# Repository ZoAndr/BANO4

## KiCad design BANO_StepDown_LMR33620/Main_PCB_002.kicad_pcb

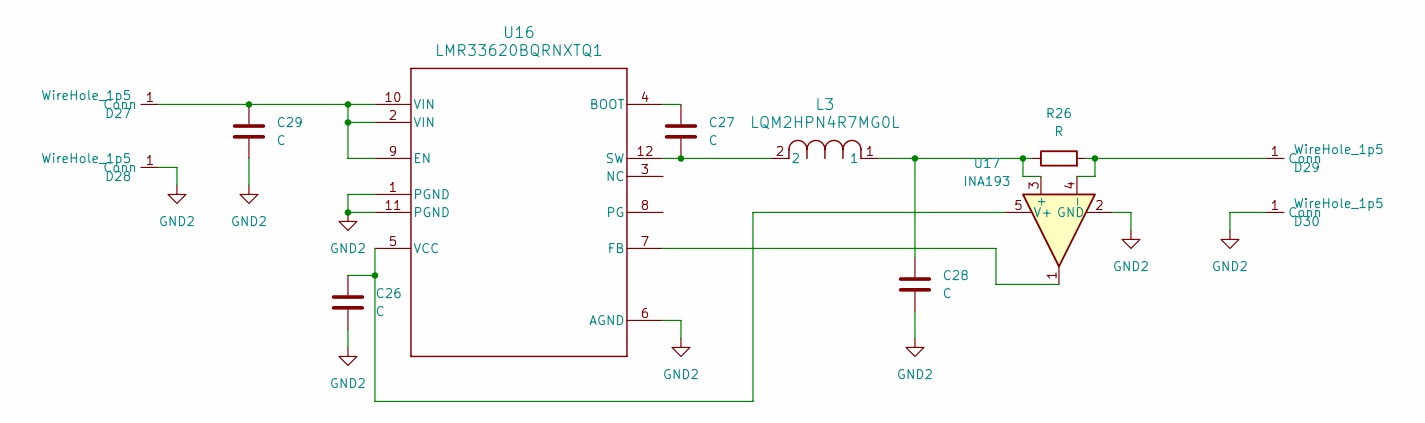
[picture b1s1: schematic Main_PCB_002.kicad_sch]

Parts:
C26, C27: C; C_0603_1608Metric_Pad1.08x0.95mm_HandSolder
C28, C29: C; C_0805_2012Metric_Pad1.18x1.45mm_HandSolder
D27, D28, D29, D30: WireHole_1p5; WireHole_1p2
L3: LQM2HPN4R7MG0L; IND_LQM2HPN4R7MG0L_MUR
R26: R; R_0603_1608Metric_Pad0.98x0.95mm_HandSolder
U16: LMR33620BQRNXTQ1; RNX0012B
U17: INA193; SOT-23-5

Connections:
GND2: C26.2, C28.2, C29.2, D28.1 (Conn), D30.1 (Conn), U16.1 (PGND), U16.6 (AGND), U16.11 (PGND), U17.2 (GND)
unnamed: C29.1, D27.1 (Conn), U16.2 (VIN), U16.9 (EN), U16.10 (VIN)
unnamed: D29.1 (Conn), R26.2, U17.4 (-)
unnamed: C27.1, U16.4 (BOOT)
unnamed: U16.7 (FB), U17.1
unnamed: C27.2, L3.2, U16.12 (SW)
unnamed: C26.1, U16.5 (VCC), U17.5 (V+)
unnamed: C28.1, L3.1, R26.1, U17.3 (+)

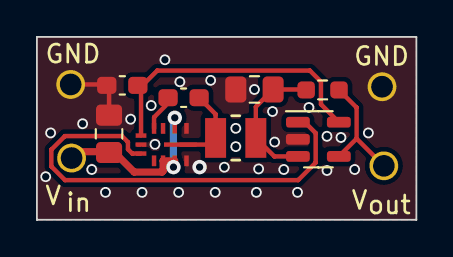
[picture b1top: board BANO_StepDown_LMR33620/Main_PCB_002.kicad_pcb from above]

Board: 2 copper layers, 21.1 x 10.2 mm, 12 parts (0 on the bottom side), 8 nets.

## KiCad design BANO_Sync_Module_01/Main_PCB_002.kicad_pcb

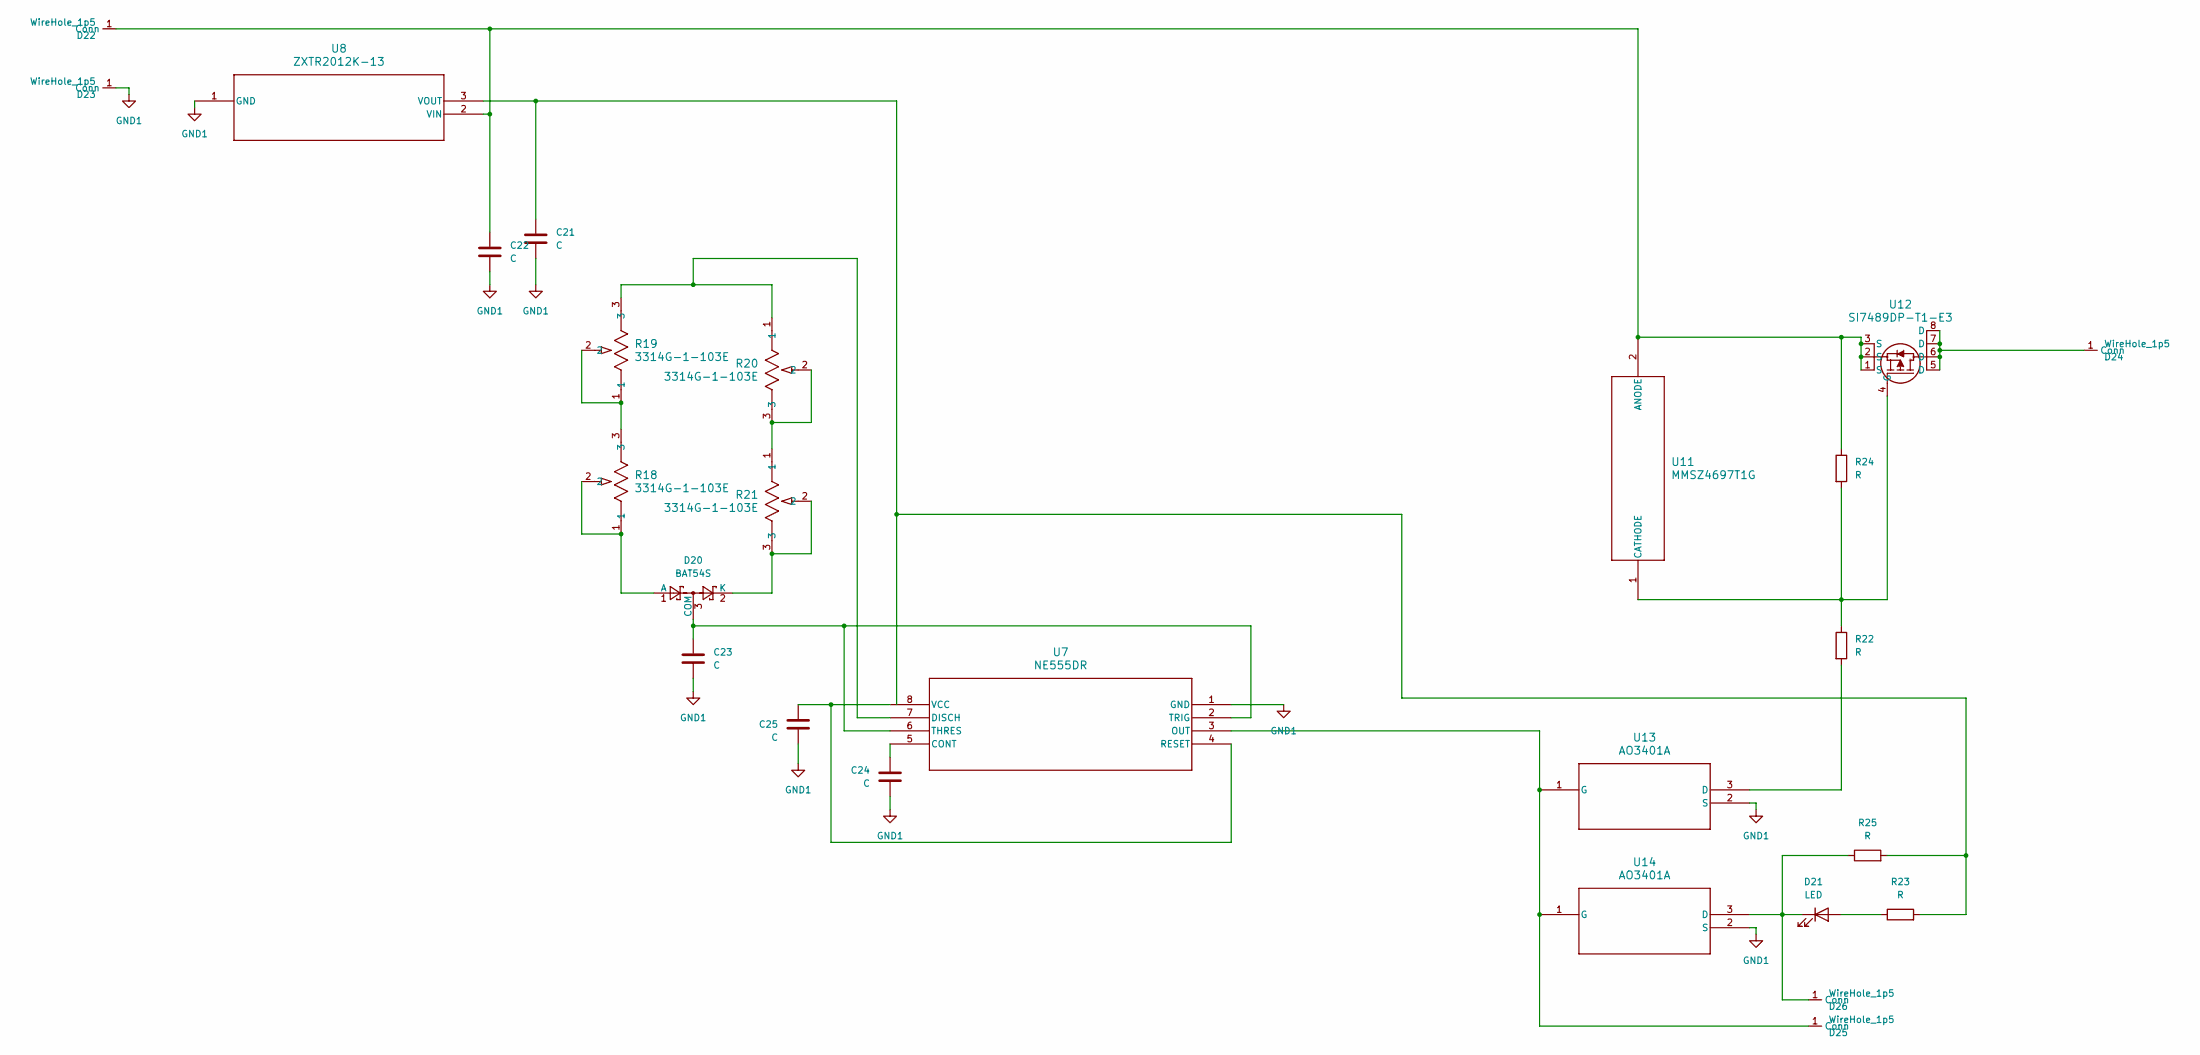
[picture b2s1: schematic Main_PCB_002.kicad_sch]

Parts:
C21, C22, C24: C; C_0603_1608Metric_Pad1.08x0.95mm_HandSolder
C23, C25: C; C_0805_2012Metric_Pad1.18x1.45mm_HandSolder
D20: BAT54S; SOT-23
D21: LED; LED_0603_1608Metric_Pad1.05x0.95mm_HandSolder
D22, D23, D24, D25, D26: WireHole_1p5; WireHole_1p2
R18, R19, R20, R21: 3314G-1-103E; POT_3314G
R22, R23, R24, R25: R; R_0603_1608Metric_Pad0.98x0.95mm_HandSolder
U7: NE555DR; D8
U8: ZXTR2012K-13; TO252-3L_DIO
U11: MMSZ4697T1G; SOD-123_ONS
U12: SI7489DP-T1-E3; MOSFET_65DP-T1-E3_VIS
U13, U14: AO3401A; SOT-23-3L_AOS

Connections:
GND1: C21.2, C22.2, C23.2, C24.2, C25.2, D23.1 (Conn), U7.1 (GND), U8.1 (GND), U13.2 (S), U14.2 (S); also elsewhere on the board
unnamed: D20.1 (A), R18.1, R18.2
unnamed: C23.1, D20.3 (COM), U7.2 (TRIG), U7.6 (THRES)
unnamed: D20.2 (K), R21.2, R21.3
unnamed: D21.2 (A), R23.1
unnamed: D21.1 (K), D26.1 (Conn), R25.1, U14.3 (D)
unnamed: C22.1, D22.1 (Conn), R24.1, U8.2 (VIN), U11.2 (ANODE), U12.1 (S), U12.2 (S), U12.3 (S)
unnamed: D24.1 (Conn), U12.5 (D), U12.6 (D), U12.7 (D), U12.8 (D)
unnamed: D25.1 (Conn), U7.3 (OUT), U13.1 (G), U14.1 (G)
unnamed: R18.3, R19.1, R19.2
unnamed: R20.2, R20.3, R21.1
unnamed: C24.1, U7.5 (CONT)
unnamed: R19.3, R20.1, U7.7 (DISCH)
unnamed: C25.1, U7.4 (RESET), U7.8 (VCC)
unnamed: C21.1, R23.2, R25.2, U8.3 (VOUT)
unnamed: R22.1, R24.2, U11.1 (CATHODE), U12.4 (G)
unnamed: R22.2, U13.3 (D)

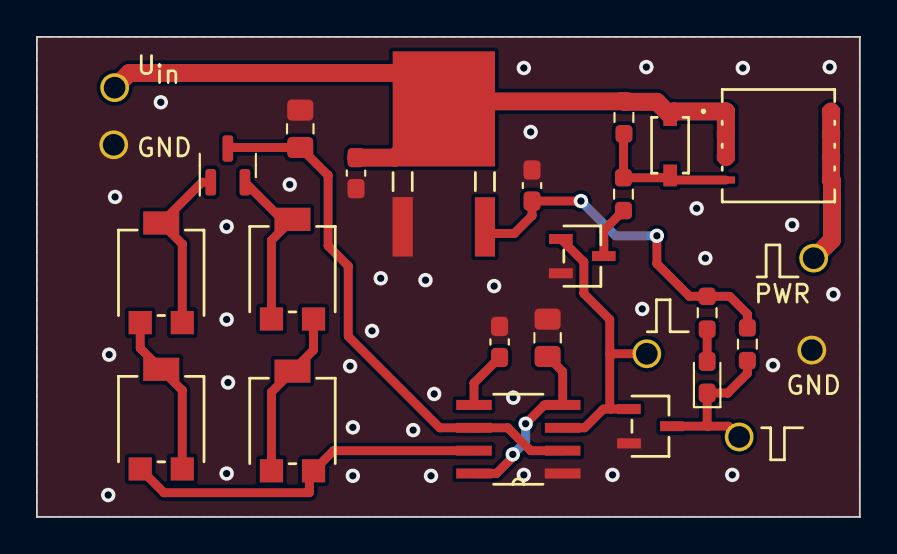
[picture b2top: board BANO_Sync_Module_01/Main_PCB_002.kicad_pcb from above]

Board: 2 copper layers, 45.7 x 26.7 mm, 27 parts (0 on the bottom side), 17 nets.

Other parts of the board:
D1: WireHole_1p5; WireHole_1p2

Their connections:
GND1: D1.1 (Conn); also elsewhere on the board

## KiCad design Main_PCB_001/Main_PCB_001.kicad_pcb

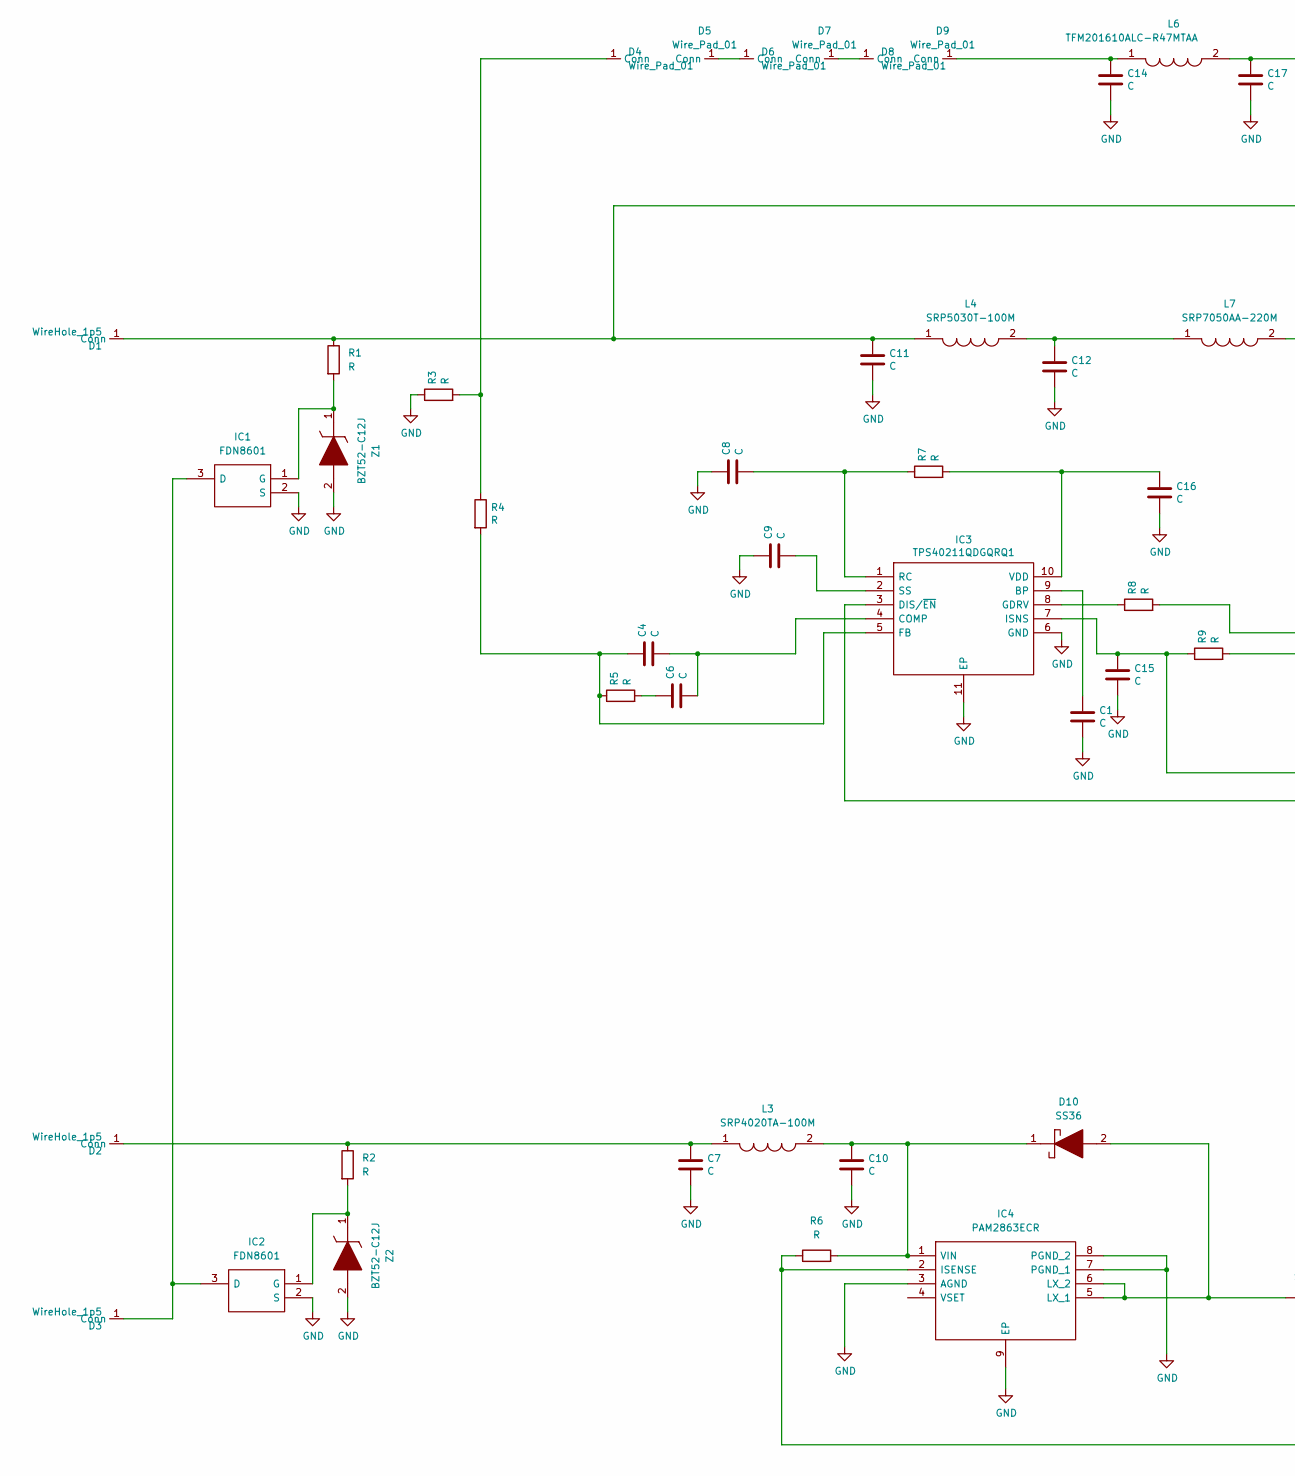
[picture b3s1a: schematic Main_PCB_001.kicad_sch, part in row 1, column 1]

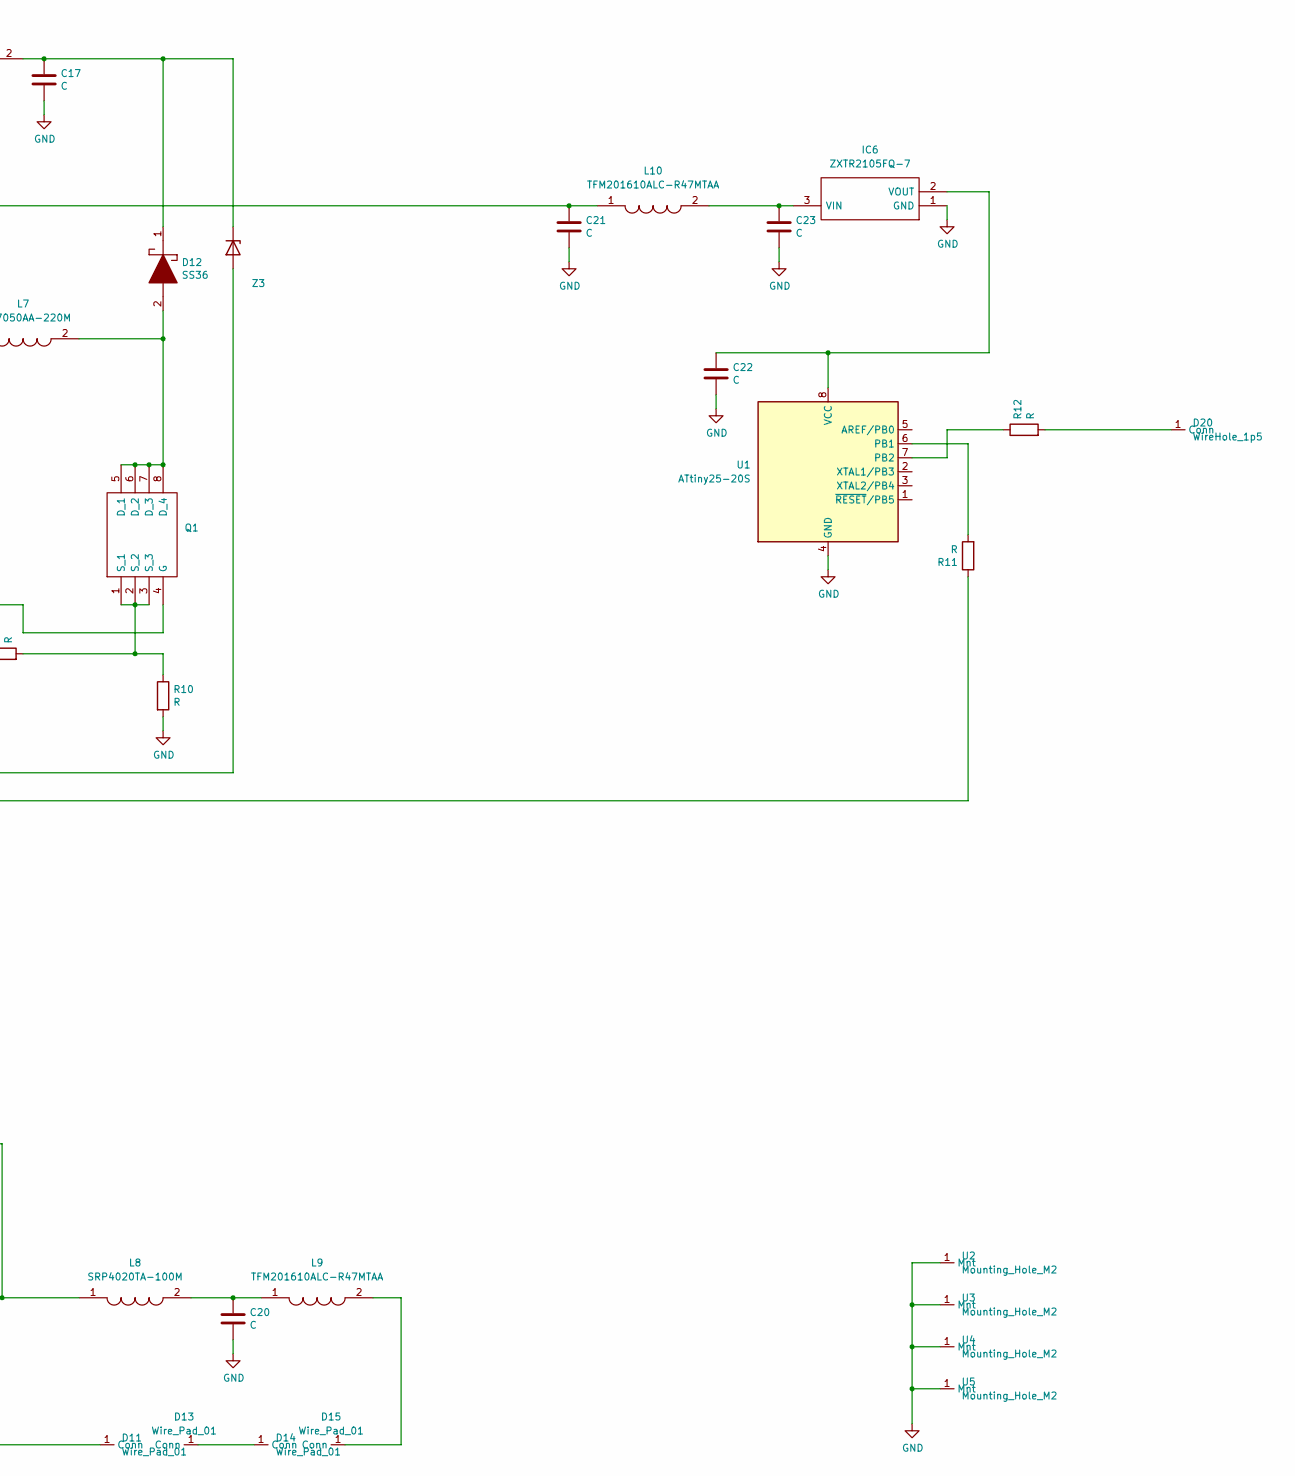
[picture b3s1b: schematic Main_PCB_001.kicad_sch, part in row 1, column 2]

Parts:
C1, C4, C6, C9, C15: C; C_0402_1005Metric_Pad0.74x0.62mm_HandSolder
C7, C11, C14, C16, C22, C23: C; C_0603_1608Metric_Pad1.08x0.95mm_HandSolder
C8: C
C10, C20: C; C_0805_2012Metric_Pad1.18x1.45mm_HandSolder
C12, C17: C; C_1206_3216Metric_Pad1.33x1.80mm_HandSolder
C21: C; C_1812_4532Metric_Pad1.57x3.40mm_HandSolder
D1, D2, D3, D20: WireHole_1p5; WireHole_1p2
D4, D5, D6, D7, D8, D9, D11, D13, D14, D15: Wire_Pad_01
D10, D12: SS36; SODFL4626X120N; Manufacturer_Part_Number SS36
IC1, IC2: FDN8601; SOT95P251X112-3N; Manufacturer_Part_Number FDN8601; Mouser Part Number 512-FDN8601
IC3: TPS40211QDGQRQ1; SOP50P490X110-11N; Manufacturer_Part_Number TPS40211QDGQRQ1; Mouser Part Number 595-TPS40211QDGQRQ1
IC4: PAM2863ECR; SOIC127P600X175-9N; Manufacturer_Part_Number PAM2863ECR; Mouser Part Number 621-PAM2863ECR
IC6: ZXTR2105FQ-7; SOT96P240X110-3N; Manufacturer_Part_Number ZXTR2105FQ-7; Mouser Part Number 621-ZXTR2105FQ-7
L3: SRP4020TA-100M; INDC2016X80N; Manufacturer_Part_Number SRP4020TA-100M; Mouser Part Number 652-SRP4020TA-100M
L4: SRP5030T-100M; INDPM4441X200N; Manufacturer_Part_Number SRP5030T-100M; Mouser Part Number 652-SRP5030T-100M
L6, L9, L10: TFM201610ALC-R47MTAA; INDC2016X80N; Manufacturer_Part_Number TFM201610ALC-R47MTAA; Mouser Part Number 810-TFM201610ALCR47M
L7: SRP7050AA-220M; INDPM5752X300N; Manufacturer_Part_Number SRP7050AA-220M; Mouser Part Number 652-SRP7050AA-220M
L8: SRP4020TA-100M; INDPM4441X200N; Manufacturer_Part_Number SRP4020TA-100M; Mouser Part Number 652-SRP4020TA-100M
Q1: Manufacturer_Part_Number AON7407
R1, R2, R10, R11, R12: R; R_0603_1608Metric_Pad0.98x0.95mm_HandSolder
R3: R; R_0805_2012Metric_Pad1.20x1.40mm_HandSolder
R4, R5, R7: R; R_0402_1005Metric_Pad0.72x0.64mm_HandSolder
R6: R; R_1206_3216Metric_Pad1.30x1.75mm_HandSolder
R8, R9: R
U1: ATtiny25-20S; SOIC-8W_5.3x5.3mm_P1.27mm
U2, U3, U4, U5: Mounting_Hole_M2; Hole_screw_M1p2
Z1, Z2: BZT52-C12J; BZT52C12J; Manufacturer_Part_Number BZT52-C12J; Mouser Part Number N/A
Z3: D_SOD-323F; Manufacturer_Part_Number BZT52-C5V1J; Mouser Part Number N/A

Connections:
GND: C1.2, C7.2, C8.1, C9.1, C10.2, C11.2, C12.2, C14.2, C15.2, C16.2, C17.2, C20.2, C21.2, C22.2, C23.2, IC1.2 (S), IC2.2 (S), IC3.6 (GND), IC3.11 (EP), IC4.3 (AGND), IC4.7 (PGND_1), IC4.8 (PGND_2), IC4.9 (EP), IC6.1 (GND), R3.1, R10.2, U1.4 (GND), U2.1 (Mnt), U3.1 (Mnt), U4.1 (Mnt), U5.1 (Mnt), Z1.2, Z2.2
unnamed: C4.1, IC3.5 (FB), R4.2, R5.1
unnamed: C4.2, C6.2, IC3.4 (COMP)
unnamed: C6.1, R5.2
unnamed: C7.1, D2.1 (Conn), L3.1, R2.1
unnamed: C8.2, IC3.1 (RC), R7.1
unnamed: C9.2, IC3.2 (SS)
unnamed: C10.1, D10.1, IC4.1 (VIN), L3.2, R6.2
unnamed: C11.1, C21.1, D1.1 (Conn), L4.1, L10.1, R1.1
unnamed: C12.1, L4.2, L7.1
unnamed: C14.1, D9.1 (Conn), L6.1
unnamed: C15.1, IC3.7 (ISNS), R9.1, Z3.2 (A)
unnamed: C16.1, IC3.10 (VDD), R7.2
unnamed: C17.1, D12.1, L6.2, Z3.1 (K)
unnamed: C20.1, L8.2, L9.1
unnamed: C22.1, IC6.2 (VOUT), U1.8 (VCC)
unnamed: C23.1, IC6.3 (VIN), L10.2
unnamed: D3.1 (Conn), IC1.3 (D), IC2.3 (D)
unnamed: D4.1 (Conn), R3.2, R4.1
unnamed: D5.1 (Conn), D6.1 (Conn)
unnamed: D7.1 (Conn), D8.1 (Conn)
unnamed: D10.2, IC4.5 (LX_1), IC4.6 (LX_2), L8.1
unnamed: D11.1 (Conn), IC4.2 (ISENSE), R6.1
unnamed: D12.2, L7.2, Q1.5 (D_1), Q1.6 (D_2), Q1.7 (D_3), Q1.8 (D_4)
unnamed: D13.1 (Conn), D14.1 (Conn)
unnamed: D15.1 (Conn), L9.2
unnamed: D20.1 (Conn), R12.2
unnamed: IC1.1 (G), R1.2, Z1.1
unnamed: IC2.1 (G), R2.2, Z2.1
unnamed: IC3.3 (DIS/~EN), R11.1
unnamed: IC3.8 (GDRV), R8.1
unnamed: C1.1, IC3.9 (BP)
unnamed: Q1.4 (G), R8.2
unnamed: Q1.1 (S_1), Q1.2 (S_2), Q1.3 (S_3), R9.2, R10.1
unnamed: R11.2, U1.6 (PB1)
unnamed: R12.1, U1.7 (PB2)

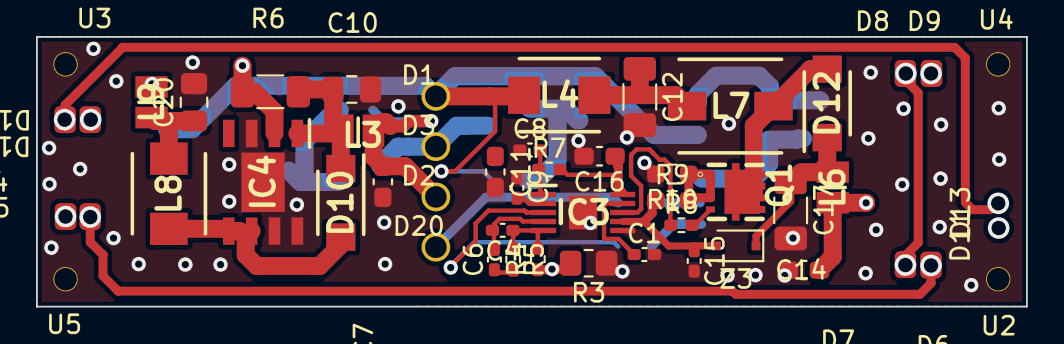
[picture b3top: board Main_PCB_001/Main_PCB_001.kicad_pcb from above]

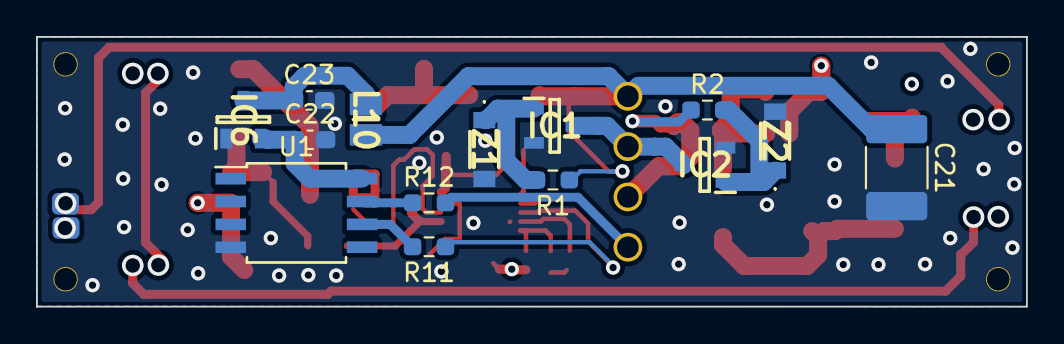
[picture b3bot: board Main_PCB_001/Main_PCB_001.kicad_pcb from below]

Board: 4 copper layers, 55.0 x 15.0 mm, 66 parts (14 on the bottom side), 36 nets.

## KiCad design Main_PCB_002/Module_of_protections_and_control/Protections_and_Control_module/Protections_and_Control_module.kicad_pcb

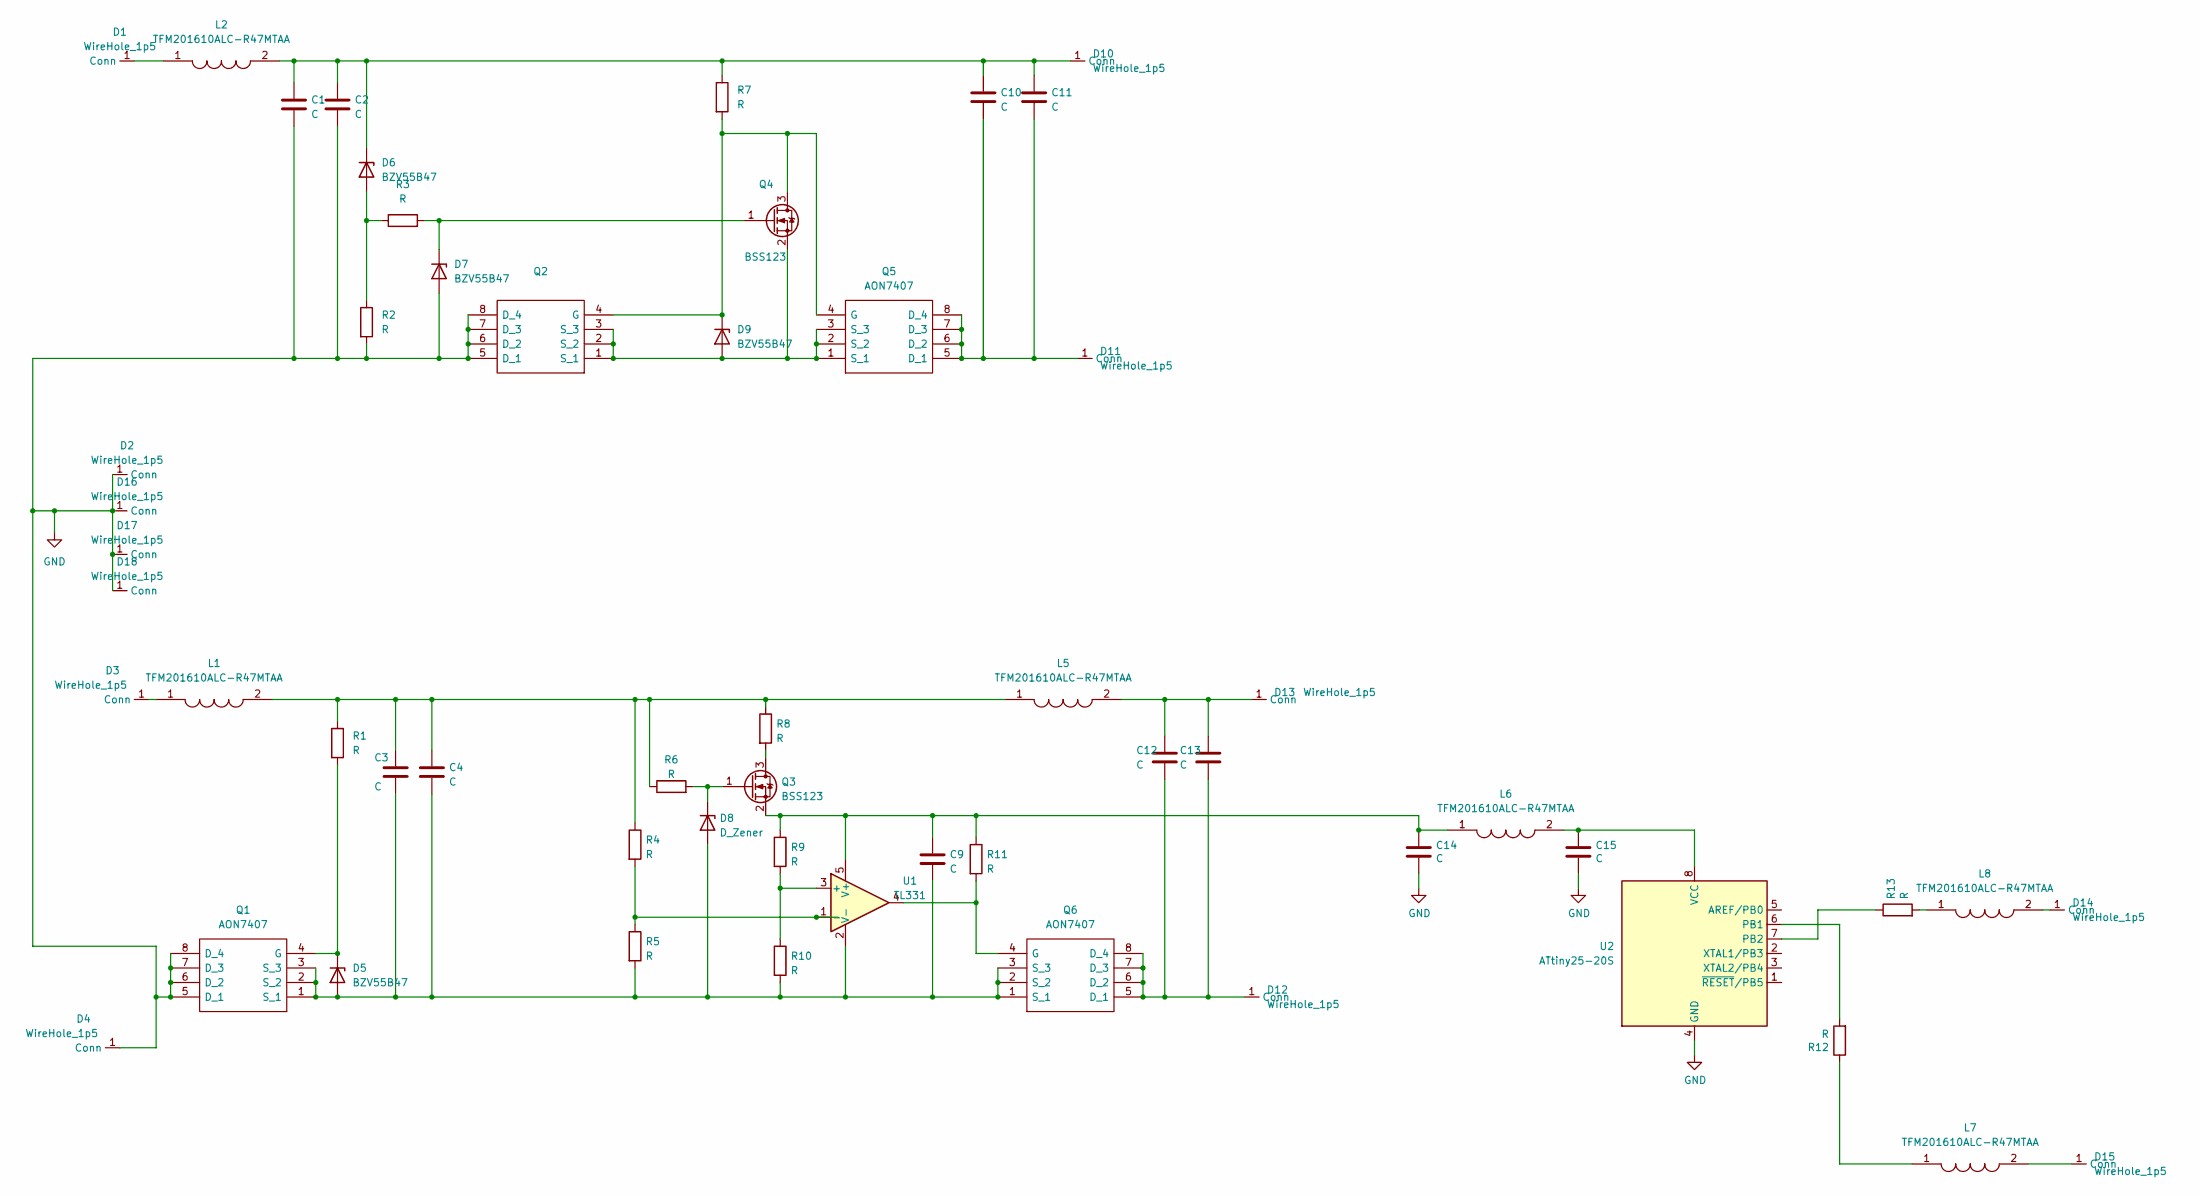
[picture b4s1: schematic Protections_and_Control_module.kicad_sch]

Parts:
C1, C3, C10, C12: C
C2, C4, C9, C11, C13: C; C_1206_3216Metric_Pad1.33x1.80mm_HandSolder
C14, C15: C; C_0603_1608Metric_Pad1.08x0.95mm_HandSolder
D1, D2, D3, D4, D15, D16, D17, D18: WireHole_1p5; WireHole_1p2
D5, D6, D7, D9: BZV55B47
D8: D_Zener; SOD2513X120N
D10, D11, D12, D13, D14: WireHole_1p5
L1, L2, L5: TFM201610ALC-R47MTAA; INDPM4442X200N; Manufacturer_Part_Number TFM201610ALC-R47MTAA; Mouser Part Number 810-TFM201610ALCR47M
L6, L7, L8: TFM201610ALC-R47MTAA; INDC2112X105N; Manufacturer_Part_Number TFM201610ALC-R47MTAA; Mouser Part Number 810-TFM201610ALCR47M
Q1, Q5, Q6: AON7407; DFN_3X3_EP; Manufacturer_Part_Number AON7407
Q2: Manufacturer_Part_Number AON7407
Q3, Q4: BSS123; SOT-23
R1, R2, R3, R4, R5, R6, R7, R8, R9, R10, R11: R
R12, R13: R; R_0603_1608Metric_Pad0.98x0.95mm_HandSolder
U1: TL331; SOT-23-5
U2: ATtiny25-20S; SOIC-8W_5.3x5.3mm_P1.27mm

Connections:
GND: C1.2, C2.2, C14.2, C15.2, D2.1 (Conn), D4.1 (Conn), D7.2 (A), D16.1 (Conn), D17.1 (Conn), D18.1 (Conn), Q1.5 (D_1), Q1.6 (D_2), Q1.7 (D_3), Q1.8 (D_4), Q1.9, Q1.10, Q1.11, Q2.5 (D_1), Q2.6 (D_2), Q2.7 (D_3), Q2.8 (D_4), Q2.9, Q2.10, Q2.11, R2.2, U2.4 (GND)
unnamed: C1.1, C2.1, C10.1, C11.1, D6.1 (K), D10.1 (Conn), L2.2, R7.1
unnamed: C3.1, C4.1, L1.2, L5.1, R1.1, R4.1, R6.1, R8.1
unnamed: C3.2, C4.2, C9.2, D5.2 (A), D8.2 (A), Q1.1 (S_1), Q1.2 (S_2), Q1.3 (S_3), Q6.1 (S_1), Q6.2 (S_2), Q6.3 (S_3), R5.2, R10.2, U1.2 (V-)
unnamed: C10.2, C11.2, D11.1 (Conn), Q5.5 (D_1), Q5.6 (D_2), Q5.7 (D_3), Q5.8 (D_4), Q5.9, Q5.10, Q5.11
unnamed: C12.1, C13.1, D13.1 (Conn), L5.2
unnamed: C12.2, C13.2, D12.1 (Conn), Q6.5 (D_1), Q6.6 (D_2), Q6.7 (D_3), Q6.8 (D_4), Q6.9, Q6.10, Q6.11
unnamed: C9.1, C14.1, L6.1, Q3.2 (S), R9.1, R11.1, U1.5 (V+)
unnamed: C15.1, L6.2, U2.8 (VCC)
unnamed: D1.1 (Conn), L2.1
unnamed: D3.1 (Conn), L1.1
unnamed: D5.1 (K), Q1.4 (G), R1.2
unnamed: D6.2 (A), R2.1, R3.1
unnamed: D7.1 (K), Q4.1 (G), R3.2
unnamed: D8.1 (K), Q3.1 (G), R6.2
unnamed: D9.1 (K), Q2.4 (G), Q4.3 (D), Q5.4 (G), R7.2
unnamed: D9.2 (A), Q2.1 (S_1), Q2.2 (S_2), Q2.3 (S_3), Q4.2 (S), Q5.1 (S_1), Q5.2 (S_2), Q5.3 (S_3)
unnamed: D14.1 (Conn), L8.2
unnamed: D15.1 (Conn), L7.2
unnamed: L7.1, R12.1
unnamed: L8.1, R13.2
unnamed: Q3.3 (D), R8.2
unnamed: Q6.4 (G), R11.2, U1.4
unnamed: R4.2, R5.1, U1.1 (-)
unnamed: R9.2, R10.1, U1.3 (+)
unnamed: R12.2, U2.6 (PB1)
unnamed: R13.1, U2.7 (PB2)

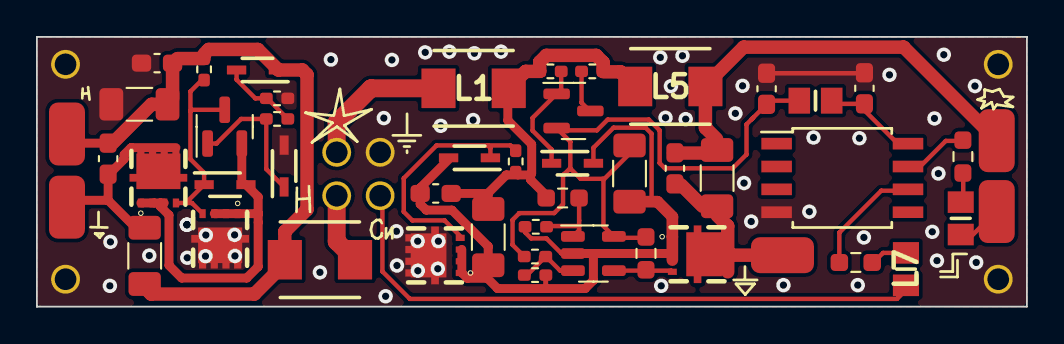
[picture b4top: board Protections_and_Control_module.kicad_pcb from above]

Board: 2 copper layers, 55.0 x 15.0 mm, 56 parts (0 on the bottom side), 27 nets.
